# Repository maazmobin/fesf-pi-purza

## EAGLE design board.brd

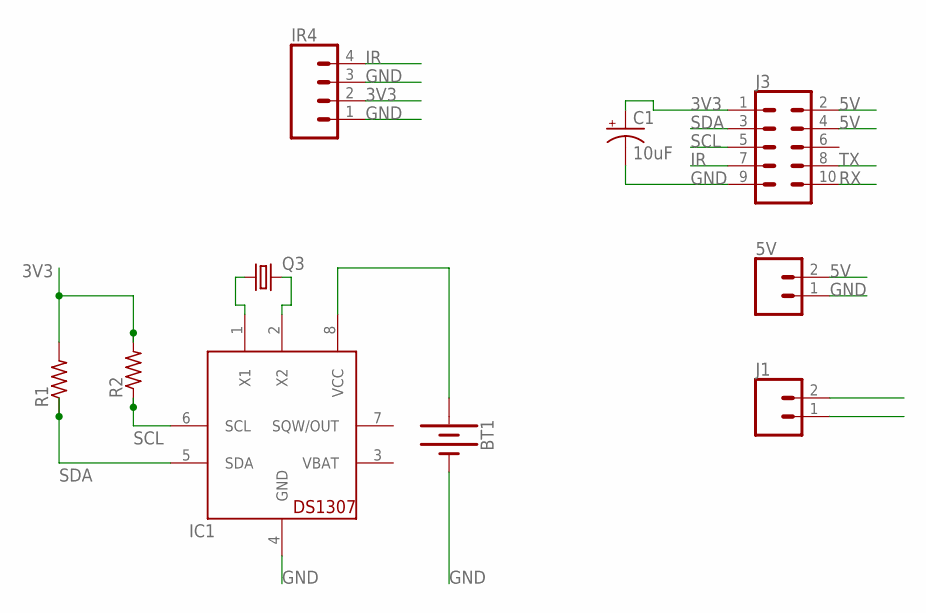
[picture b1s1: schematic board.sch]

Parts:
5V: CONN_02POLAR; MOLEX-1X2
BT1: BATTERY-20MM_PTH; BATTCOM_20MM_PTH
C1: 10uF; CPOL-RADIAL-2.5MM-5MM
IC1: DS1307; DIL08
IR4: CONN_04POLAR; MOLEX-1X4
J1: CONN_02; 1X02
J3: CONN_05X2SHD_LOCK; 2X5-SHROUDED_LOCK
Q3: CRYSTALTC38H; TC38H
R1, R2: R-US_0204/7; 0204/7

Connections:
3V3: C1.1 (+), IR4.2, J3.1, R1.2, R2.2
5V: 5V.2, J3.2, J3.4
GND: 5V.1, BT1.2 (-), C1.2 (-), IC1.4 (GND), IR4.1, IR4.3, J3.9
IR: IR4.4, J3.7
unnamed: IC1.1 (X1), Q3.1
unnamed: IC1.2 (X2), Q3.2
unnamed: BT1.1 (+), IC1.8 (VCC)
RX: J1.1, J3.10
SCL: IC1.6 (SCL), J3.5, R2.1
SDA: IC1.5 (SDA), J3.3, R1.1
TX: J1.2, J3.8
VBAT: IC1.3 (VBAT)

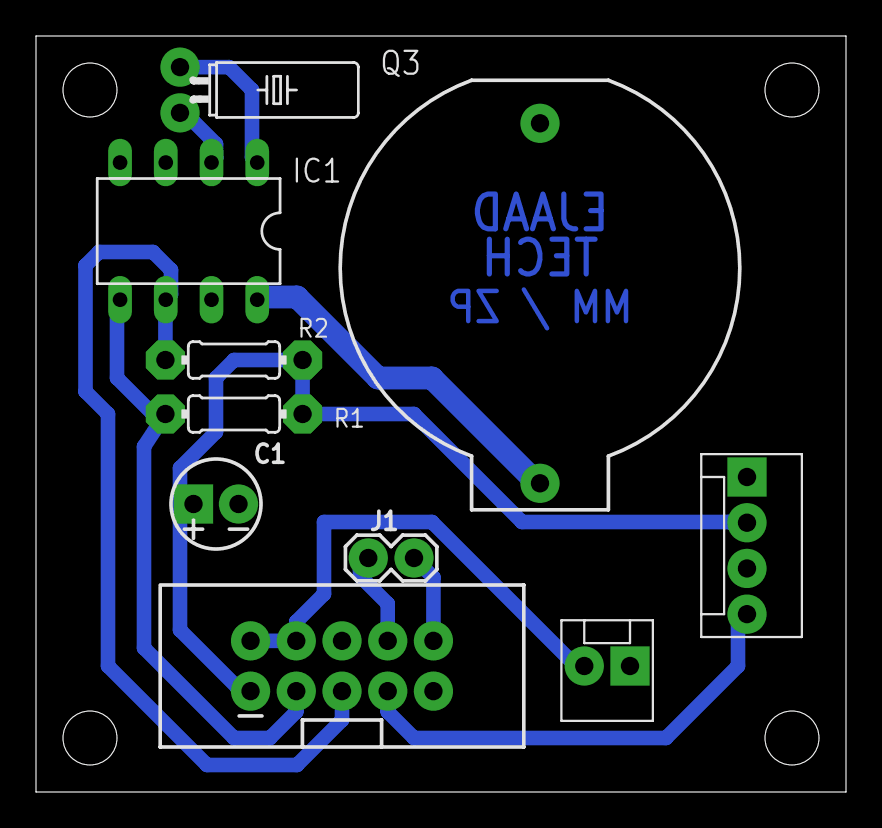
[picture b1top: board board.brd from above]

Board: 2 copper layers, 45.0 x 42.0 mm, 10 parts (0 on the bottom side), 11 nets.

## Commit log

2018-01-12 Layout complete, review required
    need silk
2018-01-12 adding layout
2018-01-26 pads edit

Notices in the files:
parts and their libraries:
SparkFun-Connectors: Licensing: Creative Commons ShareAlike 4.0 International - https://creativecommons.org/licenses/by-sa/4.0
